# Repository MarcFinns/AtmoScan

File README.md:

## AtmoScan

Instructable can be found [HERE](https://www.instructables.com/id/AtmoScan/).  
See it in action in this [VIDEO](https://www.youtube.com/watch?v=iyFuKU8ZcuA).

**What's new** - Atmoscan is evolving:

* Some small hardware changes improved the original design, including the ability to **turn off itself from software**, remediating one of the biggest drawbacks of the design - how to handle low battery. 
* Command added to the setup **menu to turn off the device**
* White screen with low battery issue **mitigation**
* A PCB v2 design is now published together with a guide to easily **apply the change to boards V1.0.**
* Battery pack now based on 5 x 18650 Li-ion in "olympic circles" configuration. Way more performant and reliable than the chinese Li-Po pack
* Repositioning of the CO2 sensor, to completely separate the temperature sensor from any potential heat source
* CAD files for the **complete enclosure**, with improved design

Atmoscan might be (to my knowledge at least) the first ESP8266 application that **uses all GPIOs**, including those that allegedly cannot be used.

**ATMOSCAN** is a multisensor device that measures:

* Temperature
* Humidity
* Pressure
* CO2
* CO
* NO2
* VOC (Air Quality indicator)
* PM 01
* PM25
* PM10
* PM 01
* Radiation

It has an LCD color display, it is gesture controlled and it posts to ThingSpeak (or others) via MQTT, but can properly handle disconnected operations. With a rechargeable battery it lasts a full day when disconnected from power.

It uses a a multitasking cooperative framework and is very responsive to user input while sampling sensors, handling UI, posting to MQTT. I believe it squeezes quite a bit out of the tiny ESP8266...

It integrates a number of open source libraries and leverages internet web services. I started buiding the software with a proper OO application framework in mind and you can find artifacts of it... but never had the time to properly finish it the way i started, so i quickly completed it with way too many hacks. Therefore code could be way better (not properly commented, test code, residuals...).  If anyone is interested in contributing, it's very welcome.

I still have a few PCBs that i am happy to give away to those who want to build it and contribute to it.

### MAIN FEATURES
```
* Color screen
* Gesture control
* Location awareness
* ThingSpeak logging        
* Gracefully handles connected and disconnected operation
* 24h Rechargeable battery
* OTA updates
* Bonus features:
	* Weather Station
	* Plane Spotter

```

### CREDITS

**INCLUDES CODE & LIBRARIES FROM**

```
Adafruit
Arcao
Bblanchon
Bodmer
ClosedCube
Gmag11
Knolleary	
Lucadentella
Seeed
Squix78
Tzapu
Wizard97	
```

**INTEGRATES WEB SERVICES FROM**

```
Adsbexchange.com
GeoNames.org
Google.com
Mylnikov.org
Timezonedb.com
Wunderground.com
```

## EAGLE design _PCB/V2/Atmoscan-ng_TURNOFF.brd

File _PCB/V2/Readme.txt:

IMPORTANT

The V2 schematic has been tested by modifying a V1 PCB and it works. The V2 PCB has been routed but has not been manufactured. I was happy enough with the modded V1. 
However i thought that if someone wanted to make Atmoscan from scratrch, it would be a good idea to provide the latest schematic with a companion PCB.
THEREFORE... before sending it blindly to your manufacturer of choice, I suggest you double check it.
Please contact me should you find any glitches. 
Happy soldering!

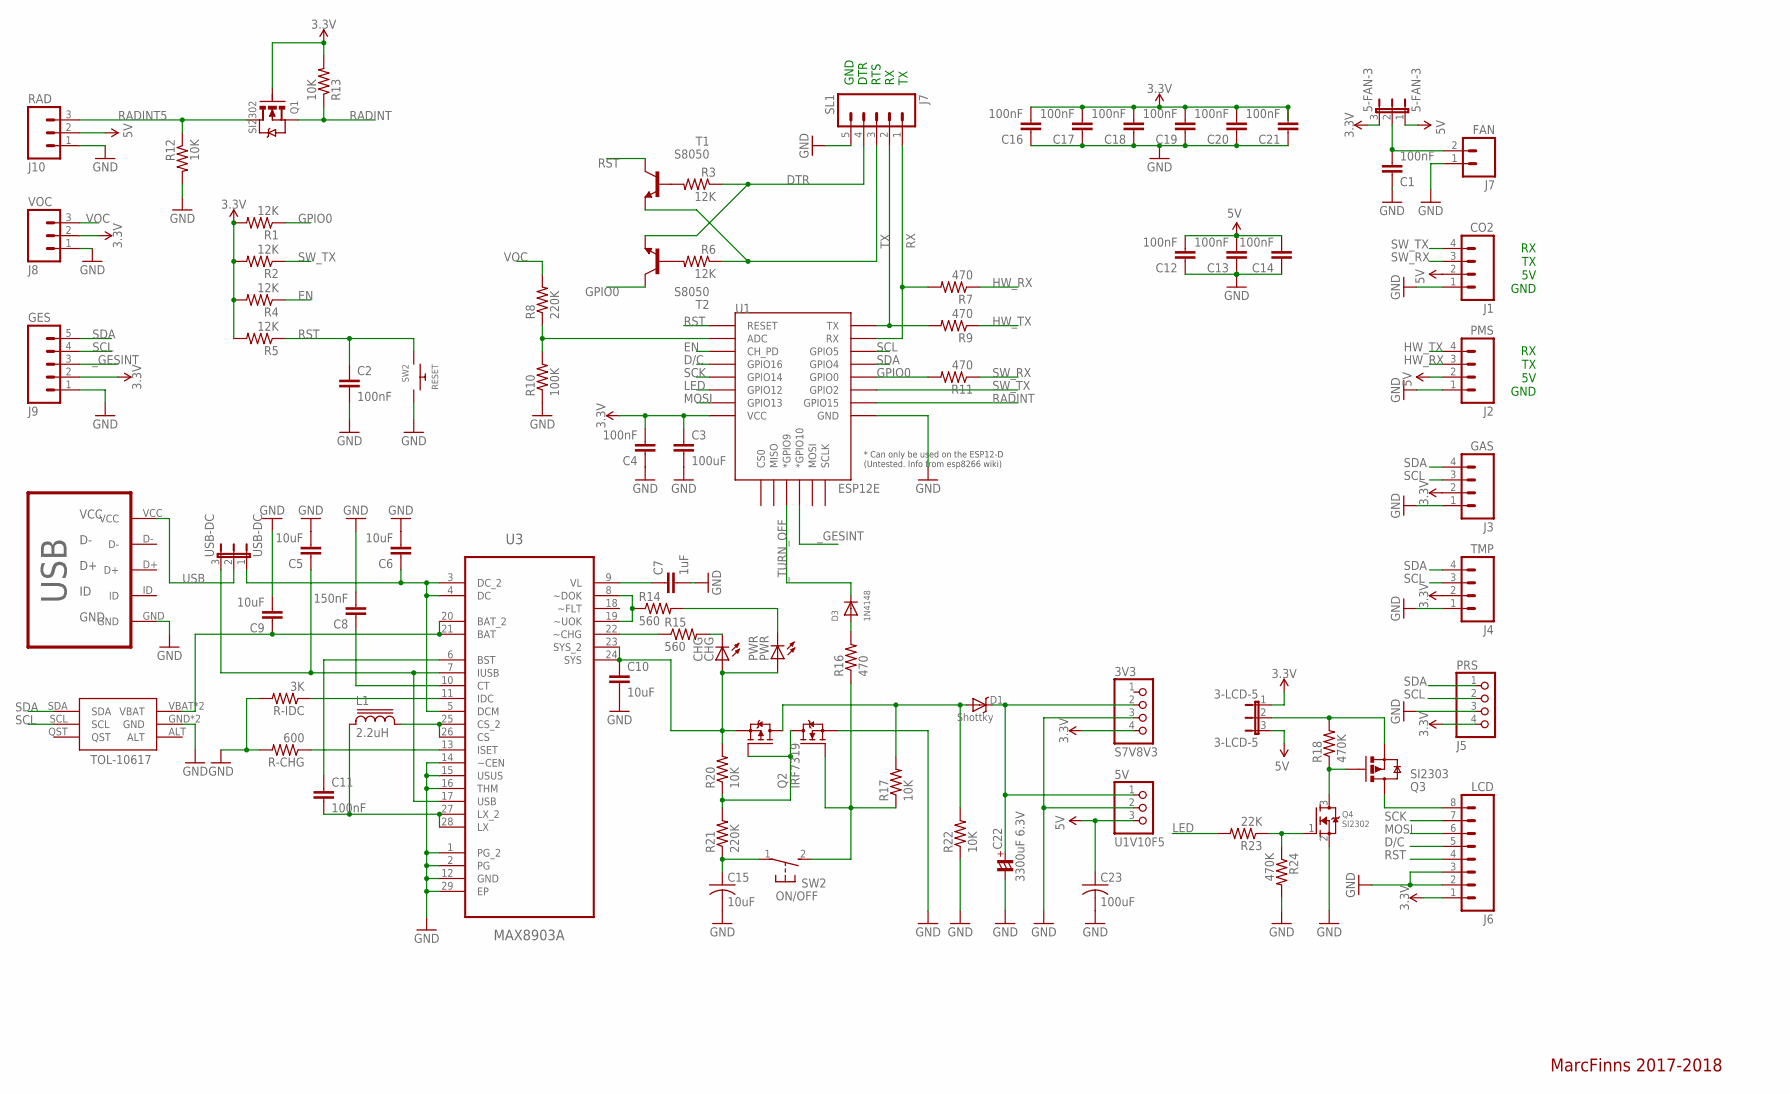
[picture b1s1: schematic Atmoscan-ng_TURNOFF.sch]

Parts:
3-LCD-5: 3-LCD-5; JP2
3V3: S7V8V3; 1X04
5-FAN-3: 5-FAN-3; JP2
5V: U1V10F5; 1X03
C1, C2, C4, C11, C12, C13, C14, C16, C17, C18, C19, C20, C21: 100nF; C0805
C3: 100uF; C0805
C5, C6, C9, C10: 10uF; C0805
C7: 1uF; C0805
C8: 150nF; C0805
C15: 10uF; C0805K
C22: 3300uF 6.3V; CE-050X100
C23: 100uF; C0805K
CHG: CHG; CHIPLED_0805
CO2: J1; 04P
D1: Shottky; SMA-403D
D3: 1N4148; SOD-123
FAN: J7; 02P
GAS: J3; 04P
GES: J9; 05P
L1: 2.2uH; SDR0503
LCD: J6; 08P
ON/OFF: SW2; B3F-31XX
PMS: J2; 04P
PRS: J5; 1X04
PWR: PWR; CHIPLED_0805
Q1: SI2302; SOT-23
Q2: IRF7319; SO08-IRF
Q3: SI2303; SOT23-3
Q4: SI2302; SOT23
R1, R2, R3, R4, R5, R6: 12K; M0805
R7, R9, R11, R16: 470; M0805
R8, R21: 220K; M0805
R10: 100K; M0805
R12, R13, R17, R20, R22: 10K; M0805
R14, R15: 560; M0805
R18, R24: 470K; M0805
R23: 22K; M0805
R-CHG: 600; M0805
R-IDC: 3K; M0805
RAD: J10; 03P
RESET: SW2; BTN_CK_KSS
SL1: J7; 05P
T1, T2: S8050; SOT23
TMP: J4; 04P
U1: ESP12E; ESP12E-SMD
U2: TOL-10617
U3: MAX8903A; QFN40P400X400X80-29N
USB: MICRO-USB-B; MICRO_USB_4_LEGS
USB-DC: USB-DC; JP2
VOC: J8; 03P

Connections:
3.3V: 3-LCD-5.1, 3V3.4, 5-FAN-3.3, C3.1, C4.2, C16.2, C17.2, C18.2, C19.2, C20.2, C21.2, GAS.2, GES.2, LCD.1, PRS.4, Q1.1 (G), R1.2, R2.2, R4.2, R5.2, R13.2, TMP.2, U1.VCC, VOC.2
5V: 3-LCD-5.3, 5-FAN-3.1, 5V.3, C12.2, C13.2, C14.2, C23.1, CO2.2, PMS.2, RAD.2
ADC: R8.1, R10.2, U1.ADC
D/C: LCD.5, U1.GPIO16
DTR: R3.1, SL1.4, T2.2 (E)
EN: R4.1, U1.CH_PD
GND: 3V3.3, 5V.2, C1.1, C2.2, C3.2, C4.1, C5.2, C6.2, C7.2, C8.2, C9.2, C10.2, C12.1, C13.1, C14.1, C15.2, C16.1, C17.1, C18.1, C19.1, C20.1, C21.1, C22.-, C23.2, CO2.1, FAN.1, GAS.1, GES.1, LCD.2, LCD.3, PMS.1, PRS.3, Q2.1 (N-S), Q4.2 (S), R10.1, R12.2, R22.1, R24.2, R-CHG.2, R-IDC.2, RAD.1, RESET.P$2, SL1.5, TMP.1, U1.GND, U2.GND, U2.GND1 (GND), U3.1 (PG_2), U3.2 (PG), U3.12 (GND), U3.14 (~CEN), U3.15 (USUS), U3.16 (THM), U3.29 (EP), USB.GND, VOC.1
GPIO0: R1.1, R11.2, T2.3 (C), U1.GPIO0
HW_RX: PMS.3, R7.1
HW_TX: PMS.4, R9.1
LED: R23.2, U1.GPIO12
MOSI: LCD.6, U1.GPIO13
unnamed: 3-LCD-5.2, Q3.2 (S), R18.2
unnamed: LCD.8, Q3.3 (D)
unnamed: C15.1, ON/OFF.1, R21.1
unnamed: C11.2, L1.1, U3.27 (LX_2), U3.28 (LX)
unnamed: C11.1, U3.6 (BST)
unnamed: C8.1, U3.10 (CT)
unnamed: Q3.1 (G), Q4.3 (D), R18.1
unnamed: R14.1, U3.8 (~DOK), U3.19 (~UOK)
unnamed: C7.1, U3.9 (VL)
unnamed: R6.2, T2.1 (B)
unnamed: D1.A, Q2.5 (P-D), Q2.6 (P-D), R17.2, R22.2
unnamed: ON/OFF.2 (S), Q2.2 (N-G), R16.1, R17.1
unnamed: Q4.1 (G), R23.1, R24.1
unnamed: R15.1, U3.22 (~CHG)
unnamed: PWR.C, R14.2
unnamed: CHG.C, R15.2
unnamed: L1.2, U3.25 (CS_2), U3.26 (CS)
unnamed: R-CHG.1, U3.13 (ISET)
unnamed: R-IDC.1, U3.11 (IDC)
unnamed: R3.2, T1.1 (B)
unnamed: 5-FAN-3.2, C1.2, FAN.2
unnamed: Q2.4 (P-G), Q2.7 (N-D), Q2.8 (N-D), R20.1, R21.2
unnamed: D3.A, R16.2
RADINT: Q1.2 (S), R13.1, U1.GPIO15
RADINT5: Q1.3 (D), R12.1, RAD.3
RST: C2.1, LCD.4, R5.1, RESET.P$1, T1.3 (C), U1.RESET
RTS: R6.1, SL1.3, T1.2 (E)
RX: R7.2, SL1.1, U1.RXD0 (RX)
SCK: LCD.7, U1.GPIO14
SCL: GAS.3, GES.4, PRS.2, TMP.3, U1.GPIO5, U2.SCL
SDA: GAS.4, GES.5, PRS.1, TMP.4, U1.GPIO4, U2.SDA
SW_RX: CO2.3, R11.1
SW_TX: CO2.4, R2.1, U1.GPIO2
SYS: C10.1, CHG.A, PWR.A, Q2.3 (P-S), R20.2, U3.23 (SYS_2), U3.24 (SYS)
TX: R9.2, SL1.2, U1.TXD0 (TX)
USB: USB.VCC, USB-DC.2
VBAT: C9.1, U2.VBAT, U2.VBAT1 (VBAT), U3.20 (BAT_2), U3.21 (BAT)
VDC: C6.1, U3.3 (DC_2), U3.4 (DC), U3.5 (DCM), USB-DC.1
VOC: R8.2, VOC.3
VUNREG: 3V3.2, 5V.1, C22.+, D1.C
VUSB: C5.1, U3.7 (IUSB), U3.17 (USB), USB-DC.3
_GESINT: GES.3, U1.GPIO10 (*GPIO10)
_TURN_OFF: D3.C, U1.GPIO9 (*GPIO9)

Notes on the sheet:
GND DTR RTS RX TX
RX TX 5V GND
MarcFinns 2017-2018

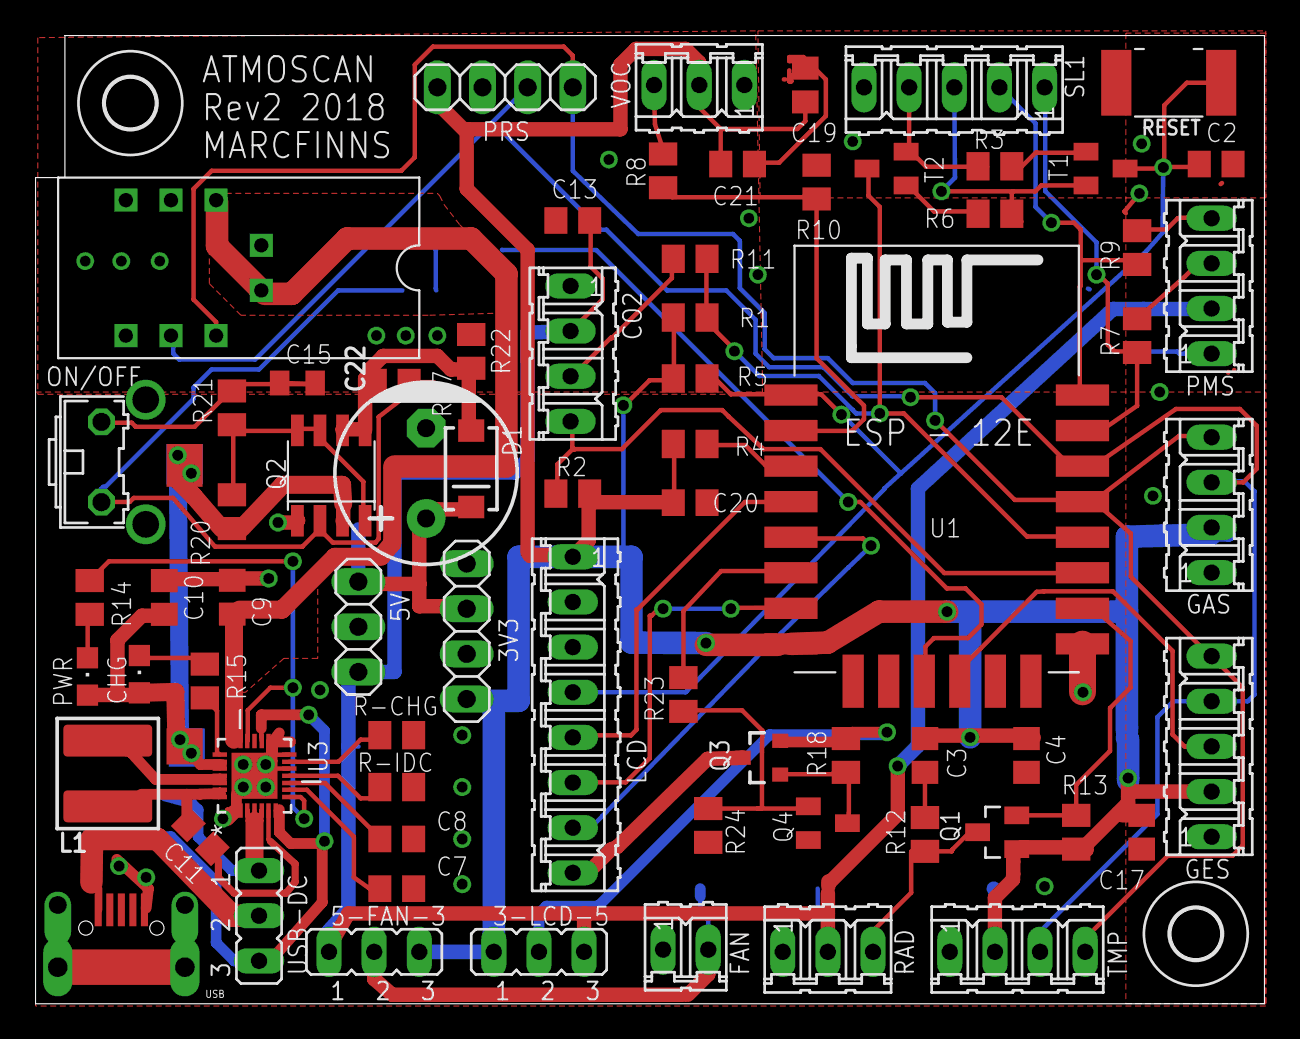
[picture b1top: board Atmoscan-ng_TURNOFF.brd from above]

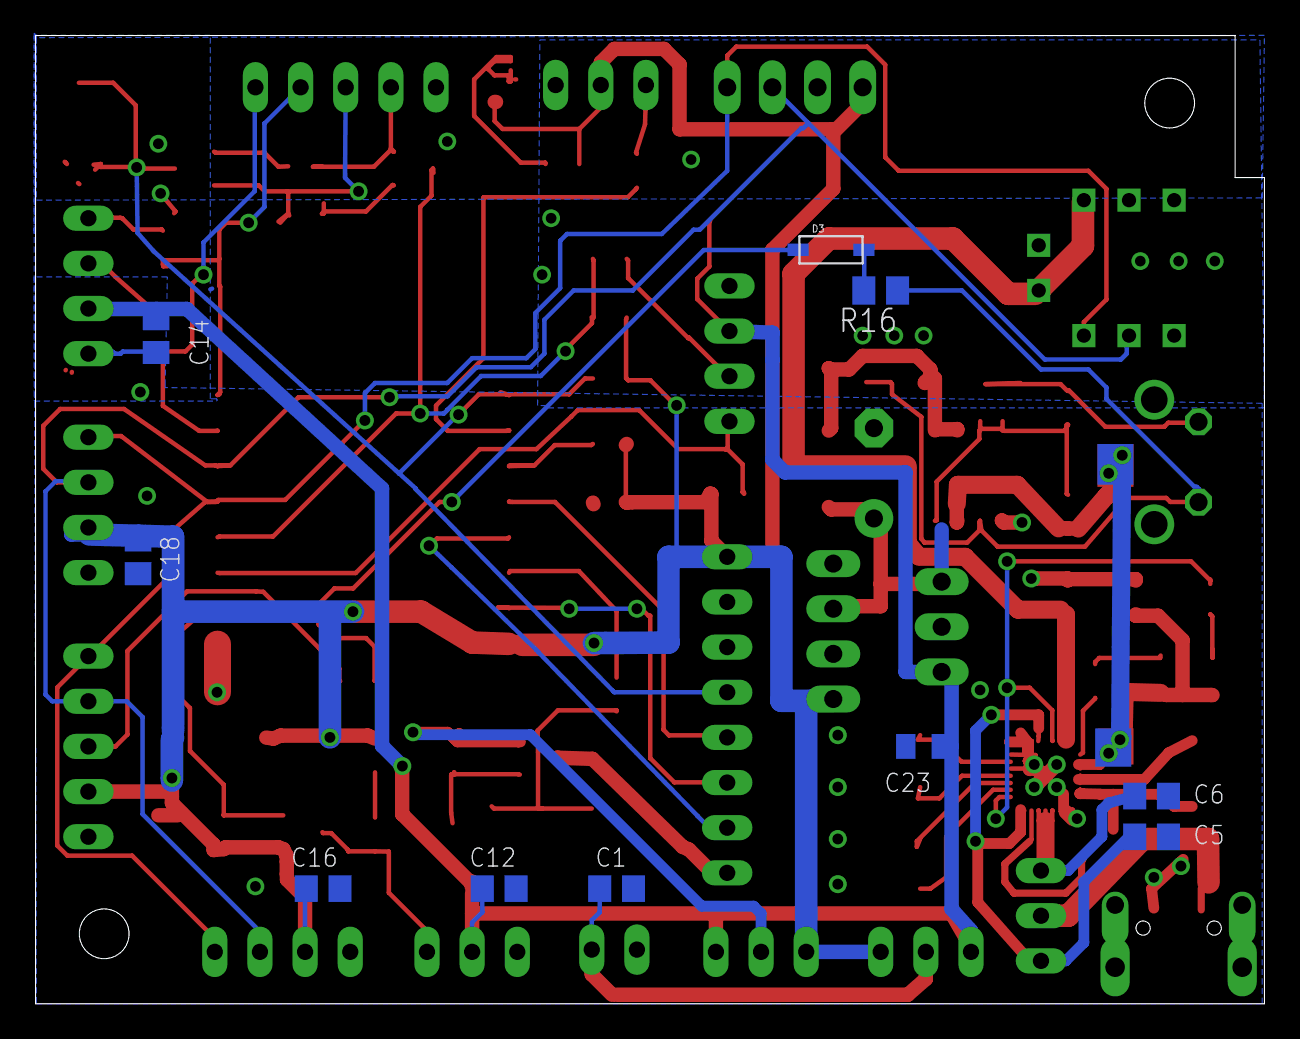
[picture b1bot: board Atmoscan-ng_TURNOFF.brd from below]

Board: 2 copper layers, 69.1 x 54.5 mm, 83 parts (10 on the bottom side), 55 nets.

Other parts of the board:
U$2, U$4: 2,8

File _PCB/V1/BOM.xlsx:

Part | Value | Device | Package | Description
3-LCD-5 | 3-LCD-5 | JP2E | JP2 | JUMPER
3V3 | S7V8V3 | PINHD-1X4 | 1X04 | PIN HEADER
5-FAN-3 | 5-FAN-3 | JP2E | JP2 | JUMPER
5V | U1V10F5 | PINHD-1X3 | 1X03 | PIN HEADER
C1 | 100nF | C-EUC0805 | C0805 | CAPACITOR, European symbol
C2 | 100nF | C-EUC0805 | C0805 | CAPACITOR, European symbol
C3 | 100uF | C-EUC0805 | C0805 | CAPACITOR, European symbol
C4 | 100nF | C-EUC0805 | C0805 | CAPACITOR, European symbol
C5 | 10uF | C-EUC0805 | C0805 | CAPACITOR, European symbol
C6 | 10uF | C-EUC0805 | C0805 | CAPACITOR, European symbol
C7 | 1uF | C-EUC0805 | C0805 | CAPACITOR, European symbol
C8 | 150nF | C-EUC0805 | C0805 | CAPACITOR, European symbol
C9 | 10uF | C-EUC0805 | C0805 | CAPACITOR, European symbol
C10 | 10uF | C-EUC0805 | C0805 | CAPACITOR, European symbol
C11 | 100nF | C-EUC0805 | C0805 | CAPACITOR, European symbol
C12 | 100nF | C-EUC0805 | C0805 | CAPACITOR, European symbol
C13 | 100nF | C-EUC0805 | C0805 | CAPACITOR, European symbol
C14 | 100nF | C-EUC0805 | C0805 | CAPACITOR, European symbol
C15 | 1uF | C-USC0805K | C0805K | CAPACITOR, American symbol
C16 | 100nF | C-EUC0805 | C0805 | CAPACITOR, European symbol
C17 | 100nF | C-EUC0805 | C0805 | CAPACITOR, European symbol
C18 | 100nF | C-EUC0805 | C0805 | CAPACITOR, European symbol
C19 | 100nF | C-EUC0805 | C0805 | CAPACITOR, European symbol
C20 | 100nF | C-EUC0805 | C0805 | CAPACITOR, European symbol
C21 | 100nF | C-EUC0805 | C0805 | CAPACITOR, European symbol
C22 | 100uF | C-USC0805K | C0805K | CAPACITOR, American symbol
C23 | 100uF | C-USC0805K | C0805K | CAPACITOR, American symbol
CHG | CHG | LEDCHIPLED_0805 | CHIPLED_0805 | LED
CO2 | J1 | M04 | 04P | AMP QUICK CONNECTOR
D1 | Shottky | DIODE-SCHOTTKYSMA-403D | SMA-403D | Commonly MBRA140.
FAN | J7 | M02 | 02P | AMP QUICK CONNECTOR
GAS | J3 | M04 | 04P | AMP QUICK CONNECTOR
GES | J9 | M05 | 05P | AMP QUICK CONNECTOR
L1 | 2.2uH | SDR0503 | SDR0503 | POWER INDUCTOR
LCD | J6 | M08 | 08P | AMP QUICK CONNECTOR
ON/OFF | SW2 | 31-XX | B3F-31XX | OMRON SWITCH
PMS | J2 | M04 | 04P | AMP QUICK CONNECTOR
PRS | J5 | PINHD-1X4 | 1X04 | PIN HEADER
PWR | PWR | LEDCHIPLED_0805 | CHIPLED_0805 | LED
Q1 | SI2302 | FET-NMOS-BSS138 | SOT-23
Q2 | IRF7319 | IRF7319 | SO08-IRF | Complimentary Half Bridge HEXFET Power MOSFET
Q3 | SI2303 | NX3008PBK | SOT23-3 | MOSFET - P Channel
Q4 | SI2302 | MOSFET-NREFLOW | SOT23 | N-Channel Mosfet
R-CHG | 600 | R-US_M0805 | M0805 | RESISTOR, American symbol
R-IDC | 3K | R-US_M0805 | M0805 | RESISTOR, American symbol
R1 | 12K | R-US_M0805 | M0805 | RESISTOR, American symbol
R2 | 12K | R-US_M0805 | M0805 | RESISTOR, American symbol
R3 | 12K | R-US_M0805 | M0805 | RESISTOR, American symbol
R4 | 12K | R-US_M0805 | M0805 | RESISTOR, American symbol
R5 | 12K | R-US_M0805 | M0805 | RESISTOR, American symbol
R6 | 12K | R-US_M0805 | M0805 | RESISTOR, American symbol
R7 | 470 | R-US_M0805 | M0805 | RESISTOR, American symbol
R8 | 220K | R-US_M0805 | M0805 | RESISTOR, American symbol
R9 | 470 | R-US_M0805 | M0805 | RESISTOR, American symbol
R10 | 100K | R-US_M0805 | M0805 | RESISTOR, American symbol
R11 | 470 | R-US_M0805 | M0805 | RESISTOR, American symbol
R12 | 10K | R-US_M0805 | M0805 | RESISTOR, American symbol
R13 | 10K | R-US_M0805 | M0805 | RESISTOR, American symbol
R14 | 560 | R-US_M0805 | M0805 | RESISTOR, American symbol
R15 | 560 | R-US_M0805 | M0805 | RESISTOR, American symbol
R17 | 10K | R-US_M0805 | M0805 | RESISTOR, American symbol
R18 | 470K | R-US_M0805 | M0805 | RESISTOR, American symbol
R20 | 10K | R-US_M0805 | M0805 | RESISTOR, American symbol
R21 | 100K | R-US_M0805 | M0805 | RESISTOR, American symbol
R22 | 10K | R-US_M0805 | M0805 | RESISTOR, American symbol
R23 | 22K | R-US_M0805 | M0805 | RESISTOR, American symbol
R24 | 470K | R-US_M0805 | M0805 | RESISTOR, American symbol
RAD | J10 | M03 | 03P | AMP QUICK CONNECTOR
RESET | SW2 | SWITCH_PUSHBUTTONC&K_KSS | BTN_CK_KSS | Buttons
SL1 | J7 | M05 | 05P | AMP QUICK CONNECTOR
T1 | S8050 | BC846 | SOT23 | NPN TRANSISTOR
T2 | S8050 | BC846 | SOT23 | NPN TRANSISTOR
TMP | J4 | M04 | 04P | AMP QUICK CONNECTOR
U1 | ESP12E | ESP12ESMD | ESP12E-SMD | ESP12E Module
U2 | TOL-10617 | TOL-10617 | TOL-10617
U3 | MAX8903A | MAX8903AETI+ | QFN40P400X400X80-29N | 2A 1-Cell Li+ DC-DC Chargers for USB and Adapter Power
USB | MICRO-USB-B | MICRO-USB-B | MICRO_USB_4_LEGS
USB-DC | USB-DC | JP2E | JP2 | JUMPER
VOC | J8 | M03 | 03P | AMP QUICK CONNECTOR

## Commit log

2018-01-20 Add files via upload
    First public upload
2018-02-03 V 1.3.0
    Added I/O indicator icon, update most libraries to latest version, some code cleanup
2018-04-24 Move sketch to appropriately named subfolder
    The Arduino IDE requires that a sketch be located in a folder of the same name. When opening a file that does not meet this sketch/folder name matching requirement the Arduino IDE presents a dialog:
    The file "__ATMOSCAN_MASTER_V2.0.ino" needs to be inside a sketch folder named "__ATMOSCAN_MASTER_V2.0".
    Create this folder, move the file, and continue?
    After clicking "OK" the Arduino IDE currently moves only the file __ATMOSCAN_MASTER_V2.0.ino to the new folder, leaving behind the other source files. This causes compilation of the sketch to fail:
    __ATMOSCAN_MASTER_V2.0.ino:1:67: fatal error: GlobalDefinitions.h: No such file or directory
    #inclu
2018-05-11 V2.2
    1. If sensors are not present/connected, they just appear disabled and the rest should work (did not test all combinations)
    2. Added an I2C scan that SYSLOGs the IDs of all devices connected to the bus. Useful for first build. Enabled when compiling with DEBUG_SYSLOG defined
    Hope it helps.
2018-05-11 Updated master to v2.2
2018-06-02 Rename file to match #include directive
    Mismatch of case between filename and #include directive causes compilation to fail in case sensitive operating systems such as Linux. Rather than correct the filename in the #include directive I hav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
2018-06-05 REL 2.3
    2.3 Release notes
    Turn off mod - allows the sketch to turn off the device, either from a command or when battery low (REQUIRES MINOR HW MOD)
    Sensors scan - those not present are disabled and boot continues
    Case fix - file names fixed to allow compilation on Linux
    NOTE: on some platforms the ESP8266 built-in SoftwareSerial support cannot be overridden by the user-level library (newer) and must be removed
2018-06-06 Updated hardware
    V2 PCB and how to implement mods to V1
2018-06-06 Full enclosure
    CAD files for full enclosure
2018-06-07 SMALL FIXES
2018-06-10 Must read comments on PCB V2
2018-06-10 Battery management
    Better averages for SoC and voltage, to take into account fluctuations because of sensors current peaks
2018-06-10 New battery back
    5 X 18650 in olympic-style arrangement
2018-06-11 Compatibility with latest TFT library
    workaround for now
2018-06-19 Code cleanup
2018-06-24 CO2 init bug fixed
2018-06-29 Cleanup of Thingspeak channels
    Channel 3 now includes the system measurements, separated from air measurements
2018-07-07 Display reset on backlit turn-on; code and comments cleanup
    Requires TFT_eSPI library version 0.20.16
2018-07-08 Geolocation just got better
    Introduced a mini state machine to execute the various steps without blocking the UI for too long
2018-07-11 PMS serial read gets better
2018-09-29 Added BuienRadar screen (Benelux rain radar)
    Added BuienRadar screen (Benelux rain radar)
    Some cleanup, still more needed
    REQUIRES ESP8266 2.4.2 (compile with 4M/2M SPIFFS)
2018-09-29 BuienRadar
    Added BuienRadar screen (Benelux rain radar)
    Some cleanup, still more needed
    REQUIRES ESP8266 2.4.2 (compile with 4M/2M SPIFFS)
2018-09-29 Some small fixes
2018-10-02 Cleanup
2018-10-14 Bug fixing
    Better SPIFFS fragmentation management
2018-10-14 Fixed SPIFFS fragmentation issues
2018-10-31 Refresh
2018-11-11 Corrected a bug on sensor init logic
    Corrected a bug on sensor init logic

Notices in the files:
parts and their libraries:
inductor-bourns: Copyright (C) 2008, Bob Starr
rc-master: Copyright (C) 2007-2008, Bob Starr
SparkFun-Aesthetics: Licensing: Creative Commons ShareAlike 4.0 International - https://creativecommons.org/licenses/by-sa/4.0
